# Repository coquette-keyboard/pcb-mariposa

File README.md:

# mariposa-pcb

mariposa is the microcontroller board for the coquette keyboard. note that this project, this board, the associated keyboard shields, and all firmware, is untested and provided with no guarantees or liability for failures, safety hazards, reguatory compliance, and/or injuries and/or losses in any form.

## bill of materials

- Raytac MTBT53-1M nRF5340 module - this is the microcontroller that runs the keyboard
- TI TPS62842DGRR DCDC converter - chosen for its 60nA quiescent current, this powers it
- TI BQ25170DSGR lipoly charger - charges the battery
- Sharp memory-in-pixel LCD that fits on top and has the 10-pin connection that matches the pinout, a few sizes should work
- 2 TI LM66100DCK ideal diode ICs - used to implement ORing between the battery and USB
- 1 TI TPS22917DBV - high side load switch for addressable RGB power. the quiescent on those things is soooooo high relative to the keeb you'll probably want to turn off power completely on battery
- 1 TI SN74LV1T125DCK - converts addressable RGB logic to input voltage for LEDs
- 1 32.768KHz 9pF load cap 3215 2-pin SMD crystal - external LFXO to reduce power use compared to internal oscillator
- 1 TI TSD05C TVS diode, protects USB VBUS input from ESD events
- 4 TI TPD4E1U06 TVS diode arrays, protects exposed data pins + USB data lines from ESD events
- 1 390pF NP0 ceramic capacitor, used to set ARGB power switch slew rate
- 1 560pF NP0 ceramic capacitor, the sharp memory display wants it, idk why
- 3 10nF 0603 ceramic capacitors, two for USB power RC filter, one for battery voltage sampling
- 8 0.1uF 0603 ceramic capacitors, used for decoupling
- 9 1uF 0603 ceramic capacitors, used for decoupling
- 3 4.7uF 1206 ceramic capacitors, used for decoupling
- 2 10uF 0805 ceramic capacitors - decopling, but more power!
- 1 R2.2 0805 thick film resistor, VBUS input surge protection
- 1 0603 1% resistor for DCDC vset, 0R - 1.8V, 1.74k - 2.2V, 21.5k - 3V, 28.7k - 3.1V, 38.3k - 3.2V, 52.3k - 3.3V – use 52.3k if you want accessories that use power to work, but 2.2V is probably the most efficient if no screen, no add-ons, no display, and no UV underglow on גחלילית או פרפר 
- 1 0603 1% resistor for charger VSET, 27k for 4.2V, 36k for 4.1V which will prolong battery longevity at the expense of runtime but this thing should last ages anyway. up to you.
- 1 2xR27 2x0603 convex resistor array - impedance matching USB data pair
- 1 0603 1% resistor for charger ISET, formula is 300/resistor in kohm = charge current in mA. i'm using 1.8k for 167mA charge current. most batteries it is dangerous to exceed 1C (charge current in mA = battery capacity in mAh)
- 2 R620 0805 thick film resistors, one for current limiting LED data output, one for current limiting status LED
- 1 2x whatever 2x0603 convex resistor array - marked as 2.2k as good value, but hard package to find so use whatever, it's just current limiting a couple button inputs as a safety measure
- 2 5.1k 0603 resistors, identify USB-C device
- 1 7.5M 0805 1% or better resistor - one leg of battery level voltage divider
- 1 15M 1206 1% or better resistor - the other leg of battery level voltage divider
- 1 2x10k or 2x4.7k (or really do some math) 2x0402 convex resistor array - optional, i2c pullups, value depends on speed
- 2 10k*4 4x0603 resistor arrays - a few uses, mostly pulling up or down pins
- 1 2xR33 2x0603 convex resistor array - terminating i2c and SWD
- 2 10uH 0603 - nRF internal DCDC
- 1 2.2uH 1008/2520 inductor - DCDC
- 2 1206 ferrites - 60-120 Ohm or so should be good, USB power and shell filtering
- 2 0805 ferrites - 240 Ohm or so is fine and better for noise, much less current here, LCD analog power filtering
- 2 G-Switch GT-TC041B-H036-L1N - side mount tactile switches for power and reset buttons
- 1 of the most common top-mount SMD USB 2.0 USB-C connector there is. take your pick, seriously, they almost all will fit but the GCT USB4105 is the one the footprint's actually meant for 
- 1 2-pin horizontal PicoBlade connector - battery input
- 1 28-pin 0.5mm pitch FFC SMD connector - output to keyboard, be sure the mounting legs will fit
- 1 10-pin 0.5mm pitch FPC SMD connector - output to LCD, be sure the mounting legs will fit
- 1 JST_SH_SM03B-SRSS-TB_1x03 or similar - ARGB output
- 1 JST_SH_SM04B-SRSS-TB_1x04 or similar - Adafruit Stemma QT-like i2c output
- 1 JST_SH_SM08B-SRSS-TB_1x08 or similar - Pimoroni SP/CE-like SPI and PWM output
- 1 shitty add-on SMD connector - for Hackaday v1.69bis shitty add ons
- 6 SK6805-EC14 ARGB LEDs - picked for the 0.25mA quiescent, still even at 0% brightness the 1.5mA total will drain a 250mAh battery in under a day. be sure you use the load switch wisely
- 1 0805 LED - for a status light. have fun!

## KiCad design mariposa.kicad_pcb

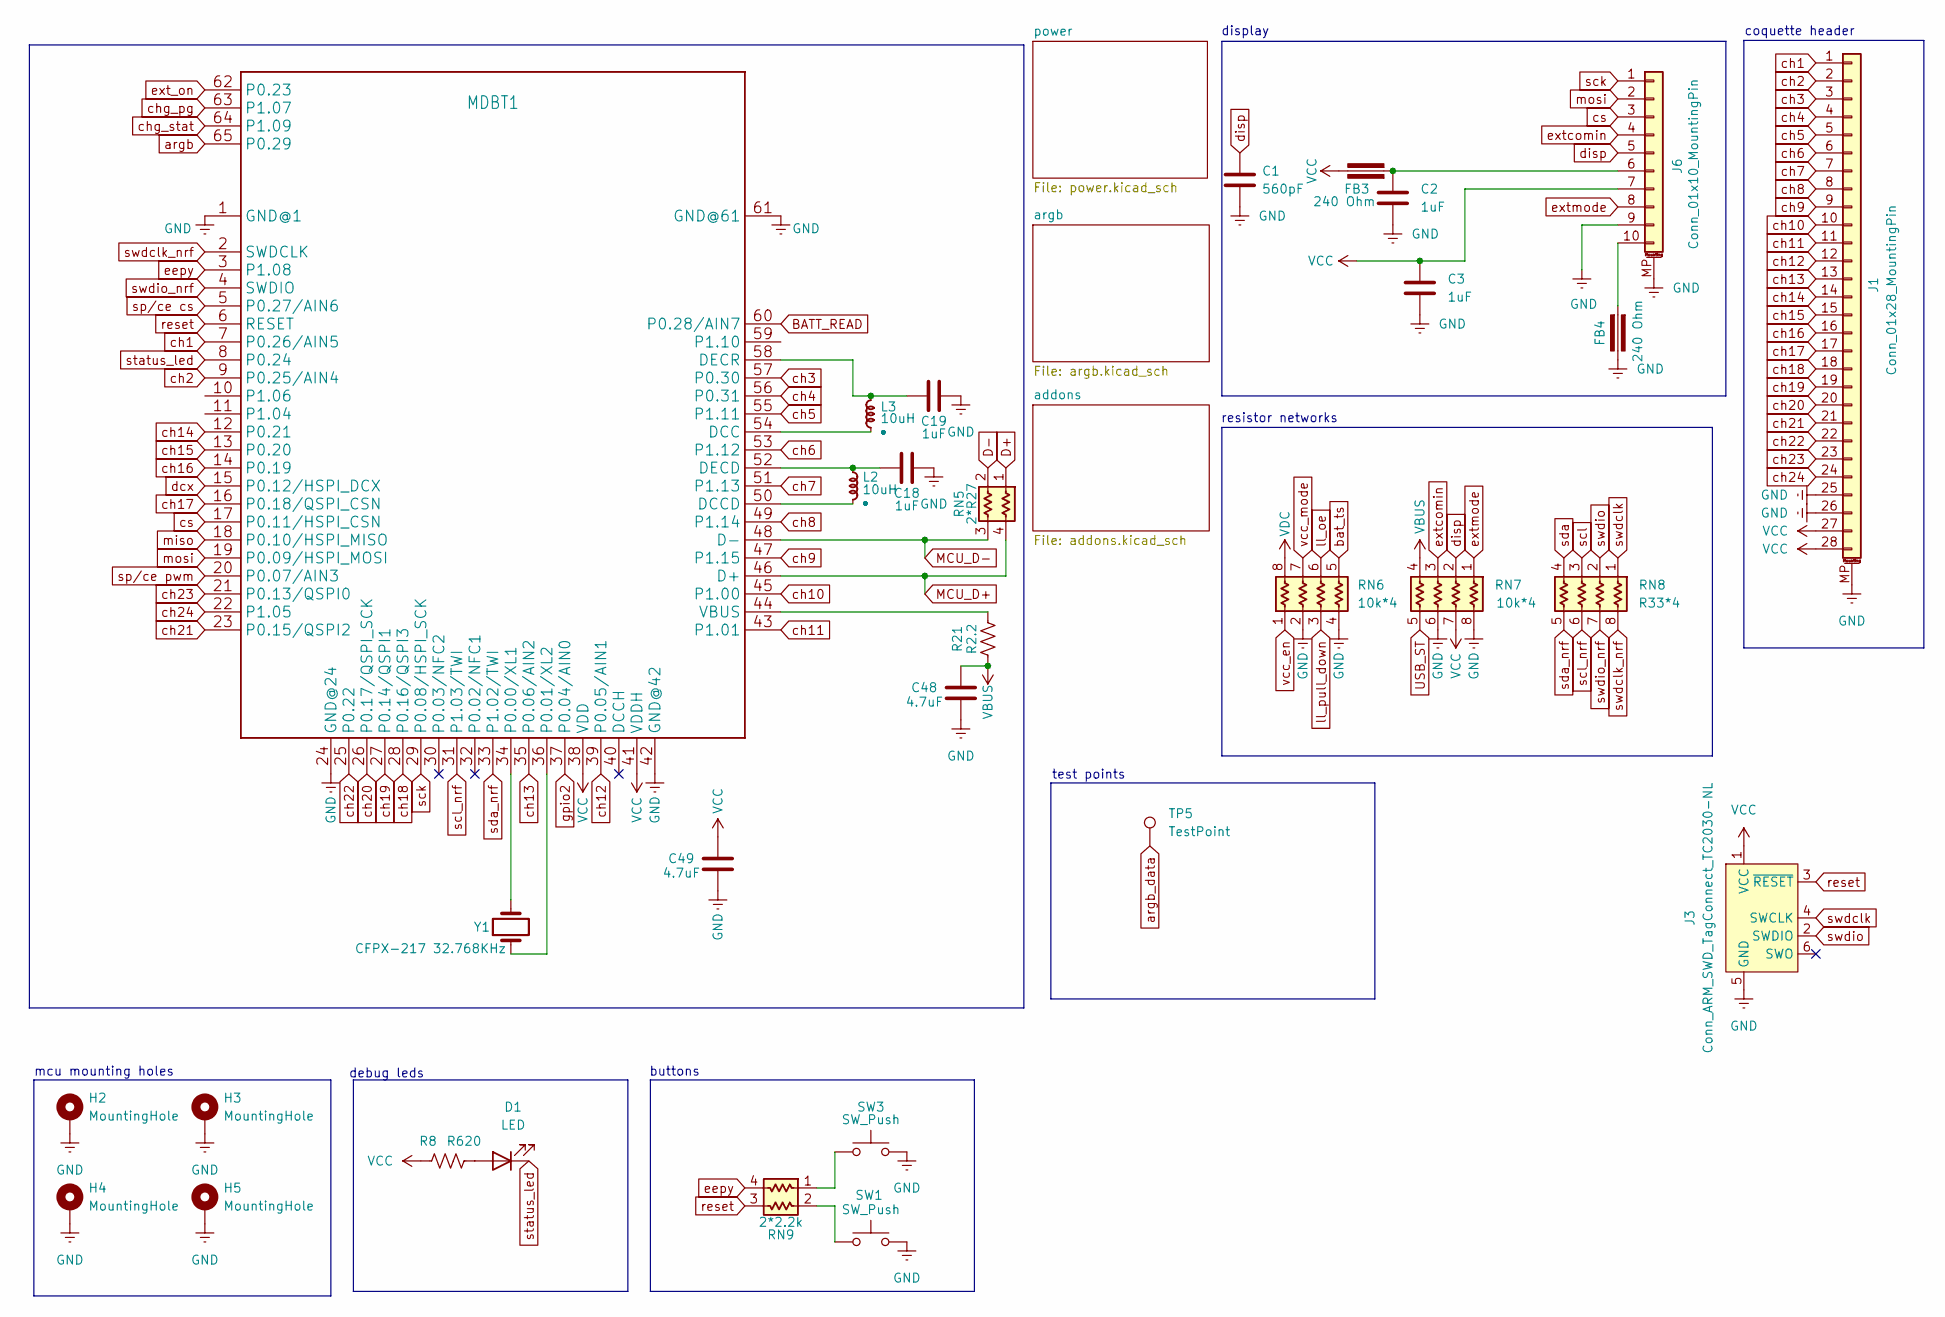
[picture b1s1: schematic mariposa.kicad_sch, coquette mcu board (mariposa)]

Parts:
C1: 560pF; C_0603_1608Metric
C2, C3, C18, C19: 1uF; C_0603_1608Metric
C48, C49: 4.7uF; C_1206_3216Metric
D1: LED; LED_0603_1608Metric
FB3, FB4: 240 Ohm; Ferrite_0603_1608Metric
H2, H3, H4, H5: MountingHole; MountingHole_3.2mm_M3_DIN965_Pad
J1: Conn_01x28_MountingPin; Hirose_FH12-28S-0.5SH_1x28-1MP_P0.50mm_Horizontal
J3: Conn_ARM_SWD_TagConnect_TC2030-NL; Tag-Connect_TC2030-IDC-NL_2x03_P1.27mm_Vertical
J6: Conn_01x10_MountingPin; Hirose_FH12-10S-0.5SH_1x10-1MP_P0.50mm_Horizontal
L2, L3: 10uH; L_0603_1608Metric
MDBT1: MDBT53
R8: R620; R_0603_1608Metric
R21: R2.2; R_0805_2012Metric
RN5: 2*R27; R_Array_Convex_2x0603
RN6, RN7: 10k*4; R_Array_Convex_4x0603
RN8: R33*4; R_Array_Convex_4x0603
RN9: 2*2.2k; R_Array_Convex_2x0603
SW1, SW3: SW_Push; G-Switch GT-TC041B-H036-L1N
TP5: TestPoint; TestPoint_Pad_D1.0mm
Y1: CFPX-217 32.768KHz; Crystal_SMD_3215-2Pin_3.2x1.5mm

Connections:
BATT_READ: MDBT1.60 (P0.28/AIN7); also elsewhere on the board
D+: RN5.1 (R1.1); also elsewhere on the board
D-: RN5.2 (R2.1); also elsewhere on the board
GND: C1.2, C2.2, C3.2, C18.1, C19.1, C48.1, C49.1, FB4.2, H2.1, H3.1, H4.1, H5.1, J1.25, J1.26, J1.MP (MountPin), J3.5 (GND), J6.9, J6.MP (MountPin), MDBT1.1 (GND@1), MDBT1.24 (GND@24), MDBT1.42 (GND@42), MDBT1.61 (GND@61), RN6.2 (R2.1), RN6.4 (R4.1), RN7.6 (R3.2), RN7.8 (R1.2), SW1.2, SW3.2; also elsewhere on the board
MCU_D+: MDBT1.46 (D+), RN5.4 (R1.2)
MCU_D-: MDBT1.48 (D-), RN5.3 (R2.2)
unnamed: D1.2 (A), R8.1
unnamed: C2.1, FB3.1, J6.6
unnamed: FB4.1, J6.10
unnamed: C18.2, L2.1 (+), MDBT1.52 (DECD)
unnamed: L2.2 (-), MDBT1.50 (DCCD)
unnamed: L3.1 (+), MDBT1.54 (DCC)
unnamed: C19.2, L3.2 (-), MDBT1.58 (DECR)
unnamed: MDBT1.34 (P0.00/XL1), Y1.2
unnamed: MDBT1.36 (P0.01/XL2), Y1.1
unnamed: MDBT1.44 (VBUS), R21.1
unnamed: RN9.1 (R1.1), SW3.1
unnamed: RN9.2 (R2.1), SW1.1
USB_ST: RN7.5 (R4.2); also elsewhere on the board
VBUS: C48.2, R21.2, RN7.4 (R4.1); also elsewhere on the board
VCC: C3.1, C49.2, FB3.2, J1.27, J1.28, J3.1 (VCC), J6.7, MDBT1.38 (VDD), MDBT1.41 (VDDH), R8.2, RN7.7 (R2.2); also elsewhere on the board
VDC: RN6.8 (R1.2); also elsewhere on the board
argb: MDBT1.65 (P0.29); also elsewhere on the board
argb_data: TP5.1; also elsewhere on the board
bat_ts: RN6.5 (R4.2); also elsewhere on the board
ch1: J1.1, MDBT1.7 (P0.26/AIN5)
ch2: J1.2, MDBT1.9 (P0.25/AIN4)
ch3: J1.3, MDBT1.57 (P0.30)
ch4: J1.4, MDBT1.56 (P0.31)
ch5: J1.5, MDBT1.55 (P1.11)
ch6: J1.6, MDBT1.53 (P1.12)
ch7: J1.7, MDBT1.51 (P1.13)
ch8: J1.8, MDBT1.49 (P1.14)
ch9: J1.9, MDBT1.47 (P1.15)
ch10: J1.10, MDBT1.45 (P1.00)
ch11: J1.11, MDBT1.43 (P1.01)
ch12: J1.12, MDBT1.39 (P0.05/AIN1)
ch13: J1.13, MDBT1.35 (P0.06/AIN2)
ch14: J1.14, MDBT1.12 (P0.21)
ch15: J1.15, MDBT1.13 (P0.20)
ch16: J1.16, MDBT1.14 (P0.19)
ch17: J1.17, MDBT1.16 (P0.18/QSPI_CSN)
ch18: J1.18, MDBT1.28 (P0.16/QSPI3)
ch19: J1.19, MDBT1.27 (P0.14/QSPI1)
ch20: J1.20, MDBT1.26 (P0.17/QSPI_SCK)
ch21: J1.21, MDBT1.23 (P0.15/QSPI2)
ch22: J1.22, MDBT1.25 (P0.22)
ch23: J1.23, MDBT1.21 (P0.13/QSPI0)
ch24: J1.24, MDBT1.22 (P1.05)
chg_pg: MDBT1.63 (P1.07); also elsewhere on the board
chg_stat: MDBT1.64 (P1.09); also elsewhere on the board
cs: J6.3, MDBT1.17 (P0.11/HSPI_CSN)
dcx: MDBT1.15 (P0.12/HSPI_DCX)
disp: C1.1, J6.5, RN7.2 (R2.1)
eepy: MDBT1.3 (P1.08), RN9.4 (R1.2)
ext_on: MDBT1.62 (P0.23); also elsewhere on the board
extcomin: J6.4, RN7.3 (R3.1)
extmode: J6.8, RN7.1 (R1.1)
gpio2: MDBT1.37 (P0.04/AIN0); also elsewhere on the board
ll_oe: RN6.6 (R3.2); also elsewhere on the board
ll_pull_down: RN6.3 (R3.1); also elsewhere on the board
miso: MDBT1.18 (P0.10/HSPI_MISO); also elsewhere on the board
mosi: J6.2, MDBT1.19 (P0.09/HSPI_MOSI); also elsewhere on the board
reset: J3.3 (~RESET), MDBT1.6 (RESET), RN9.3 (R2.2); also elsewhere on the board
sck: J6.1, MDBT1.29 (P0.08/HSPI_SCK); also elsewhere on the board
scl: RN8.3 (R3.1); also elsewhere on the board
scl_nrf: MDBT1.31 (P1.03/TWI), RN8.6 (R3.2)
sda: RN8.4 (R4.1); also elsewhere on the board
sda_nrf: MDBT1.33 (P1.02/TWI), RN8.5 (R4.2)
sp/ce cs: MDBT1.5 (P0.27/AIN6); also elsewhere on the board
sp/ce pwm: MDBT1.20 (P0.07/AIN3); also elsewhere on the board
status_led: D1.1 (K), MDBT1.8 (P0.24)
swdclk: J3.4 (SWCLK), RN8.1 (R1.1); also elsewhere on the board
swdclk_nrf: MDBT1.2 (SWDCLK), RN8.8 (R1.2)
swdio: J3.2 (SWDIO), RN8.2 (R2.1); also elsewhere on the board
swdio_nrf: MDBT1.4 (SWDIO), RN8.7 (R2.2)
vcc_en: RN6.1 (R1.1); also elsewhere on the board
vcc_mode: RN6.7 (R2.2); also elsewhere on the board

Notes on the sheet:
buttons
test points
display
coquette header
mcu mounting holes
debug leds
resistor networks

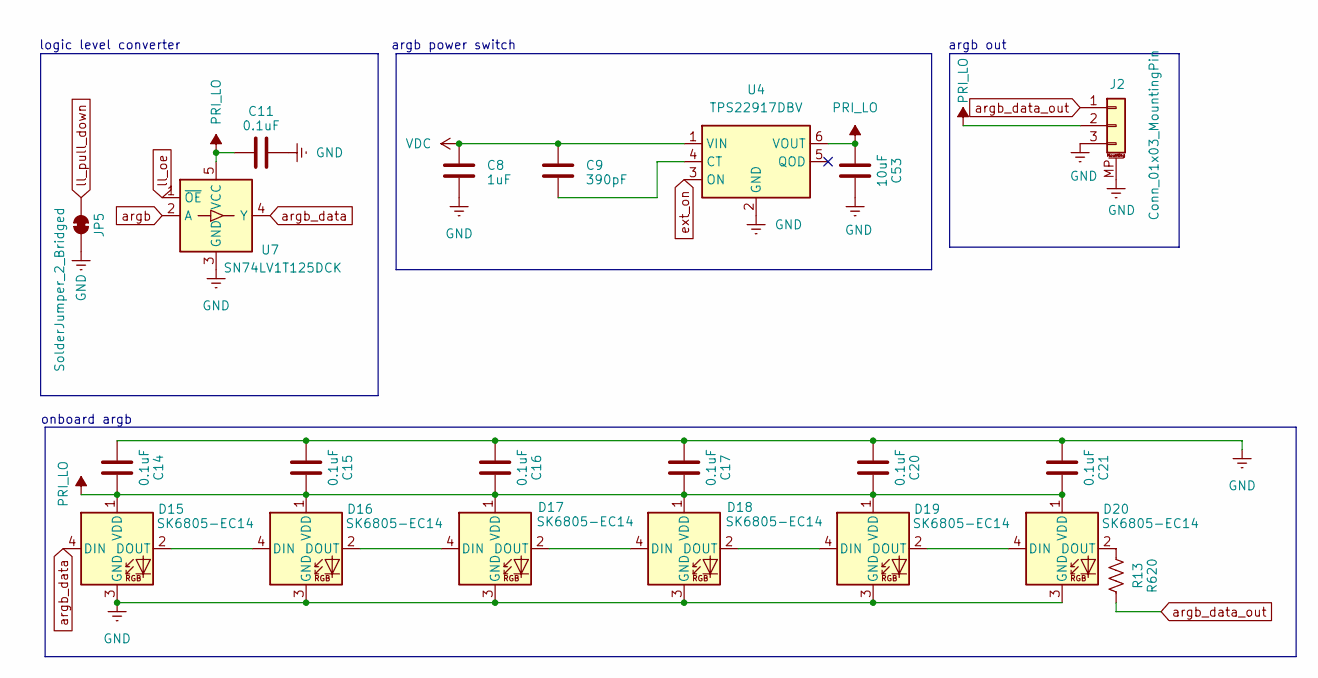
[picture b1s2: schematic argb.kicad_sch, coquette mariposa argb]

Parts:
C8: 1uF; C_0603_1608Metric
C9: 390pF; C_0603_1608Metric
C11, C14, C15, C16, C17, C20, C21: 0.1uF; C_0603_1608Metric
C53: 10uF; C_0603_1608Metric
D15, D16, D17, D18, D19, D20: SK6805-EC14
J2: Conn_01x03_MountingPin; JST_SH_SM03B-SRSS-TB_1x03-1MP_P1.00mm_Horizontal
JP5: SolderJumper_2_Bridged; SolderJumper-2_P1.3mm_Bridged_RoundedPad1.0x1.5mm
R13: R620; R_0603_1608Metric
U4: TPS22917DBV
U7: SN74LV1T125DCK

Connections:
GND: C8.2, C11.2, C14.1, C15.1, C16.1, C17.1, C20.1, C21.1, C53.2, D15.3 (GND), D16.3 (GND), D17.3 (GND), D18.3 (GND), D19.3 (GND), D20.3 (GND), J2.3, J2.MP (MountPin), JP5.2 (B), U4.2 (GND), U7.3 (GND); also elsewhere on the board
unnamed: D15.2 (DOUT), D16.4 (DIN)
unnamed: D16.2 (DOUT), D17.4 (DIN)
unnamed: D17.2 (DOUT), D18.4 (DIN)
unnamed: D18.2 (DOUT), D19.4 (DIN)
unnamed: D19.2 (DOUT), D20.4 (DIN)
unnamed: D20.2 (DOUT), R13.2
unnamed: C9.2, U4.4 (CT)
PRI_LO: C11.1, C14.2, C15.2, C16.2, C17.2, C20.2, C21.2, C53.1, D15.1 (VDD), D16.1 (VDD), D17.1 (VDD), D18.1 (VDD), D19.1 (VDD), D20.1 (VDD), J2.2, U4.6 (VOUT), U7.5 (VCC)
VDC: C8.1, C9.1, U4.1 (VIN); also elsewhere on the board
argb: U7.2 (A); also elsewhere on the board
argb_data: D15.4 (DIN), U7.4 (Y); also elsewhere on the board
argb_data_out: J2.1, R13.1; also elsewhere on the board
ext_on: U4.3 (ON); also elsewhere on the board
ll_oe: U7.1 (~OE); also elsewhere on the board
ll_pull_down: JP5.1 (A); also elsewhere on the board

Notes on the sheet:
onboard argb
argb power switch
logic level converter
argb out

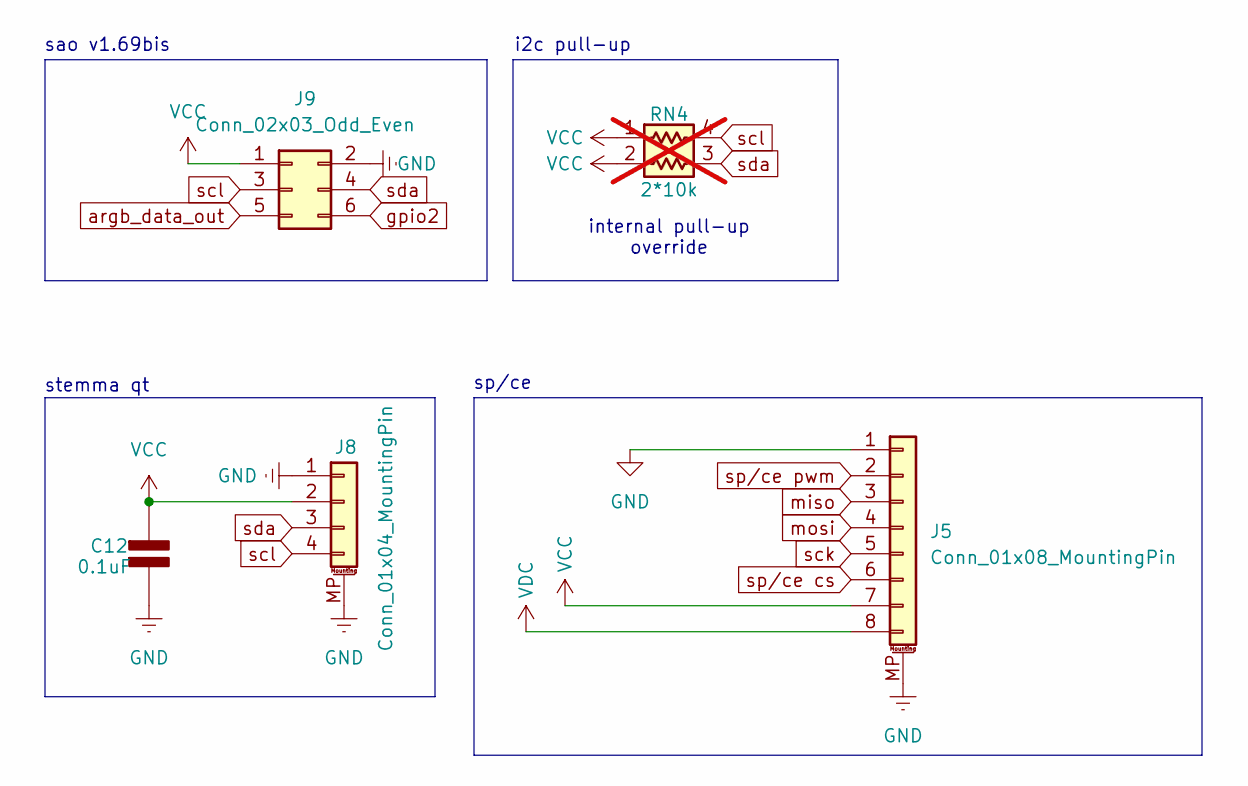
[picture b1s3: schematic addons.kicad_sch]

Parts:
C12: 0.1uF; C_0603_1608Metric; Rating V
J5: Conn_01x08_MountingPin; JST_SH_SM08B-SRSS-TB_1x08-1MP_P1.00mm_Horizontal
J8: Conn_01x04_MountingPin; JST_SH_SM04B-SRSS-TB_1x04-1MP_P1.00mm_Horizontal
J9: Conn_02x03_Odd_Even; PinSocket_2x03_P2.54mm_Vertical_SMD
RN4: 2*10k; R_Array_Convex_2x0402; not fitted

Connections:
GND: C12.2 (-), J5.1, J5.MP (MountPin), J8.1, J8.MP (MountPin), J9.2; also elsewhere on the board
VCC: C12.1 (+), J5.7, J8.2, J9.1, RN4.1 (R1.1), RN4.2 (R2.1); also elsewhere on the board
VDC: J5.8; also elsewhere on the board
argb_data_out: J9.5; also elsewhere on the board
gpio2: J9.6; also elsewhere on the board
miso: J5.3; also elsewhere on the board
mosi: J5.4; also elsewhere on the board
sck: J5.5; also elsewhere on the board
scl: J8.4, J9.3, RN4.4 (R1.2); also elsewhere on the board
sda: J8.3, J9.4, RN4.3 (R2.2); also elsewhere on the board
sp/ce cs: J5.6; also elsewhere on the board
sp/ce pwm: J5.2; also elsewhere on the board

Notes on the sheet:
sao v1.69bis
stemma qt
sp/ce
internal pull-up override
i2c pull-up

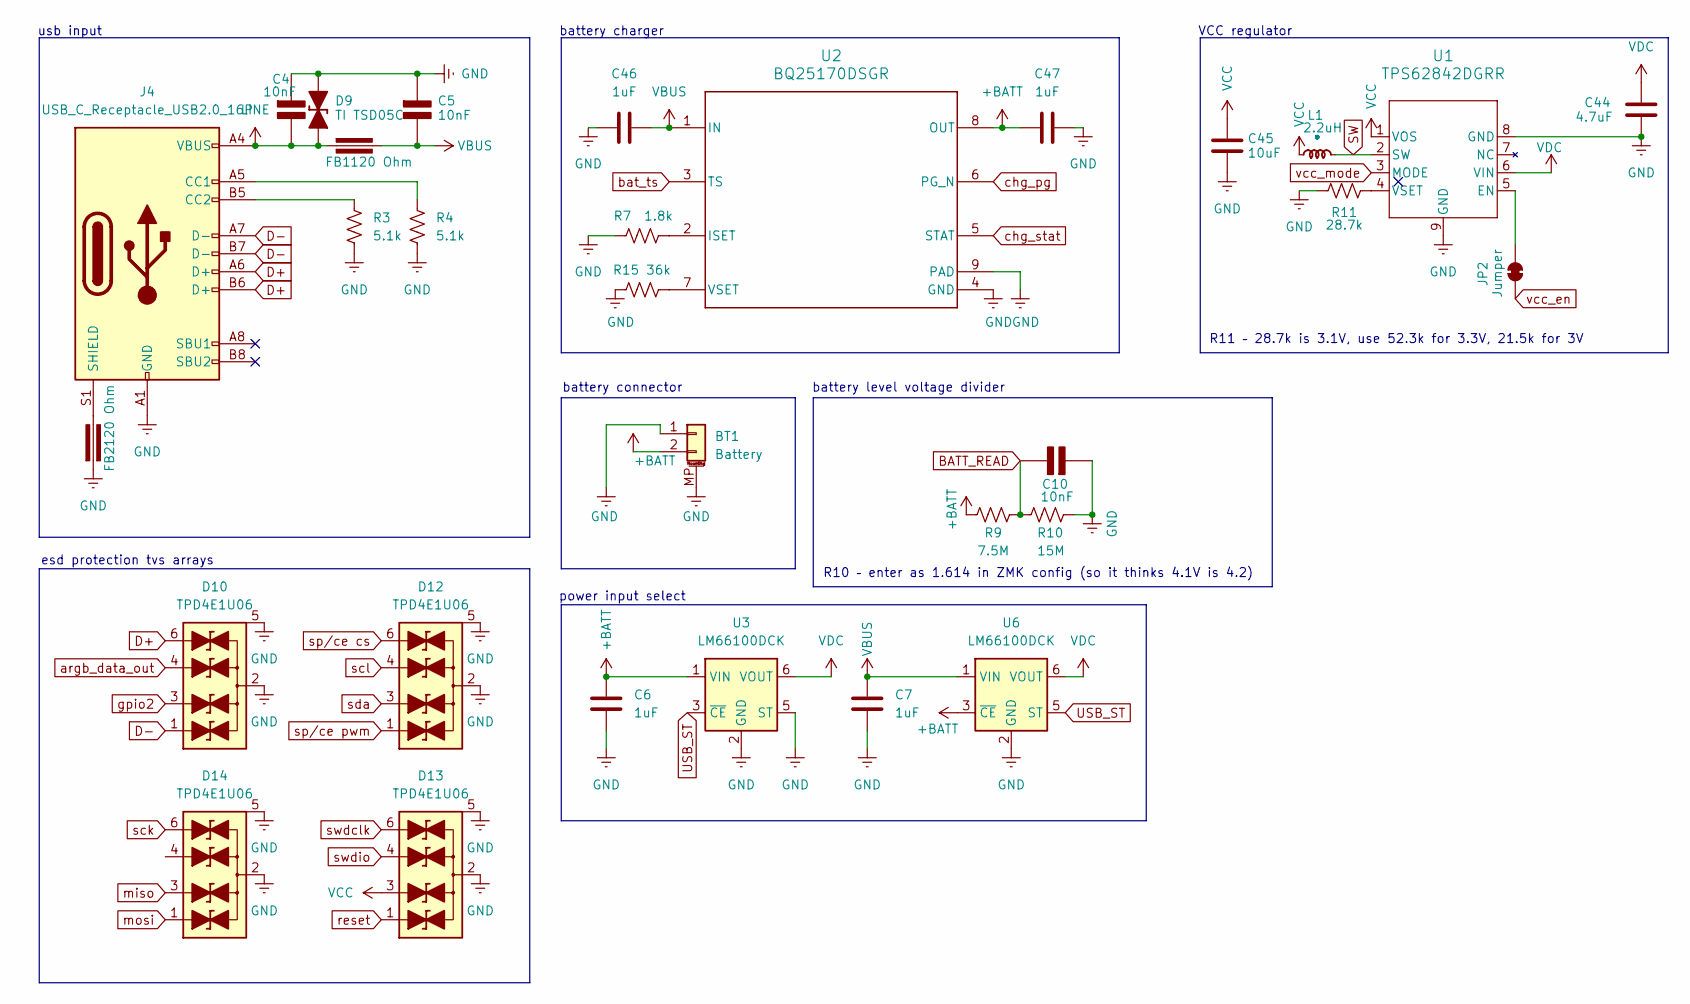
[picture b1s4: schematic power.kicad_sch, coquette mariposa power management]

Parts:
BT1: Battery; Molex_PicoBlade_53261-0271_1x02-1MP_P1.25mm_Horizontal
C4, C5, C10: 10nF; C_0603_1608Metric; Rating V
C6, C7, C46, C47: 1uF; C_0603_1608Metric
C44: 4.7uF; C_1206_3216Metric
C45: 10uF; C_0805_2012Metric
D9: TI TSD05C; TSD05C
D10, D12, D13, D14: TPD4E1U06
FB1, FB2: 120 Ohm; Ferrite_1206_3216Metric
J4: USB_C_Receptacle_USB2.0_16P; USB_C_Receptacle_GCT_USB4105-xx-A_16P_TopMnt_Horizontal
JP2: Jumper; SolderJumper-2_P1.3mm_Bridged_RoundedPad1.0x1.5mm
L1: 2.2uH; L_1008_2520Metric
R3, R4: 5.1k; R_0603_1608Metric
R7: 1.8k; R_0603_1608Metric
R9: 7.5M; R_0603_1608Metric
R10: 15M; R_1206_3216Metric
R11: 28.7k; R_0603_1608Metric
R15: 36k; R_0603_1608Metric
U1: TPS62842DGRR; HVSSOP-8-1EP_3x3mm_P0.65mm_EP1.57x1.89mm_ThermalVias
U2: BQ25170DSGR; DSG0008A
U3, U6: LM66100DCK

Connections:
+BATT: BT1.2, C6.1, C47.1, R9.2, U2.8 (OUT), U3.1 (VIN), U6.3 (~CE)
BATT_READ: C10.1 (+), R9.1, R10.2; also elsewhere on the board
D+: D10.6 (L4), J4.A6 (D+), J4.B6 (D+); also elsewhere on the board
D-: D10.1 (L1), J4.A7 (D-), J4.B7 (D-); also elsewhere on the board
GND: BT1.1, BT1.MP (MountPin), C4.1 (+), C5.1 (+), C6.2, C7.2, C10.2 (-), C44.2, C45.2, C46.1, C47.2, D9.1 (K), D10.2 (VN), D10.5 (NC), D12.2 (VN), D12.5 (NC), D13.2 (VN), D13.5 (NC), D14.2 (VN), D14.5 (NC), FB2.1, J4.A1 (GND), J4.A12 (GND), J4.B1 (GND), J4.B12 (GND), R3.2, R4.2, R7.2, R10.1, R11.2, R15.2, U1.8 (GND), U1.9 (GND), U2.4 (GND), U2.9 (PAD), U3.2 (GND), U3.5 (ST), U6.2 (GND); also elsewhere on the board
LINE: C4.2 (-), D9.2 (A), FB1.1, J4.A4 (VBUS), J4.A9 (VBUS), J4.B4 (VBUS), J4.B9 (VBUS)
unnamed: J4.A5 (CC1), R4.1
unnamed: J4.B5 (CC2), R3.1
unnamed: FB2.2, J4.S1 (SHIELD)
unnamed: JP2.1 (A), U1.5 (EN)
unnamed: R11.1, U1.4 (VSET)
unnamed: R7.1, U2.2 (ISET)
unnamed: R15.1, U2.7 (VSET)
SW: L1.2 (-), U1.2 (SW)
USB_ST: U3.3 (~CE), U6.5 (ST); also elsewhere on the board
VBUS: C5.2 (-), C7.1, C46.2, FB1.2, U2.1 (IN), U6.1 (VIN); also elsewhere on the board
VCC: C45.1, D13.3 (L2), L1.1 (+), U1.1 (VOS); also elsewhere on the board
VDC: C44.1, U1.6 (VIN), U3.6 (VOUT), U6.6 (VOUT); also elsewhere on the board
argb_data_out: D10.4 (L3); also elsewhere on the board
bat_ts: U2.3 (TS); also elsewhere on the board
chg_pg: U2.6 (PG_N); also elsewhere on the board
chg_stat: U2.5 (STAT); also elsewhere on the board
gpio2: D10.3 (L2); also elsewhere on the board
miso: D14.3 (L2); also elsewhere on the board
mosi: D14.1 (L1); also elsewhere on the board
reset: D13.1 (L1); also elsewhere on the board
sck: D14.6 (L4); also elsewhere on the board
scl: D12.4 (L3); also elsewhere on the board
sda: D12.3 (L2); also elsewhere on the board
sp/ce cs: D12.6 (L4); also elsewhere on the board
sp/ce pwm: D12.1 (L1); also elsewhere on the board
swdclk: D13.6 (L4); also elsewhere on the board
swdio: D13.4 (L3); also elsewhere on the board
vcc_en: JP2.2 (B); also elsewhere on the board
vcc_mode: U1.3 (MODE); also elsewhere on the board

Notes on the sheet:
R11 – 28.7k is 3.1V, use 52.3k for 3.3V, 21.5k for 3V
esd protection tvs arrays
R10 – enter as 1.614 in ZMK config (so it thinks 4.1V is 4.2)
battery connector
battery charger
power input select
usb input
battery level voltage divider
VCC regulator

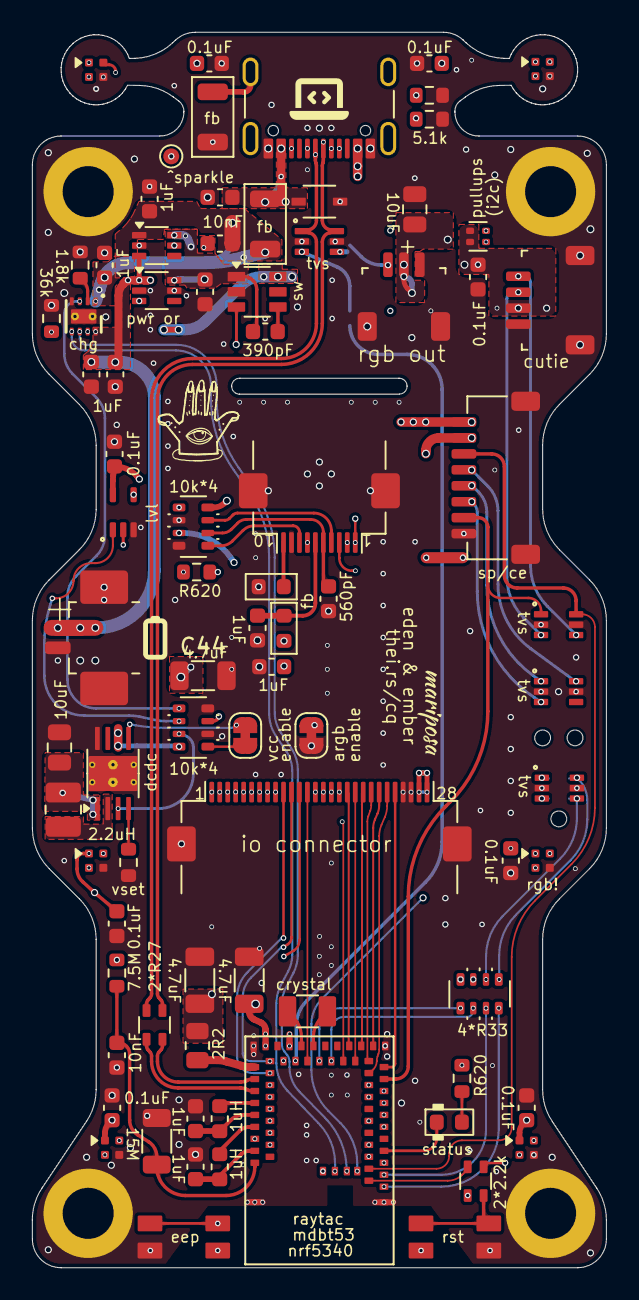
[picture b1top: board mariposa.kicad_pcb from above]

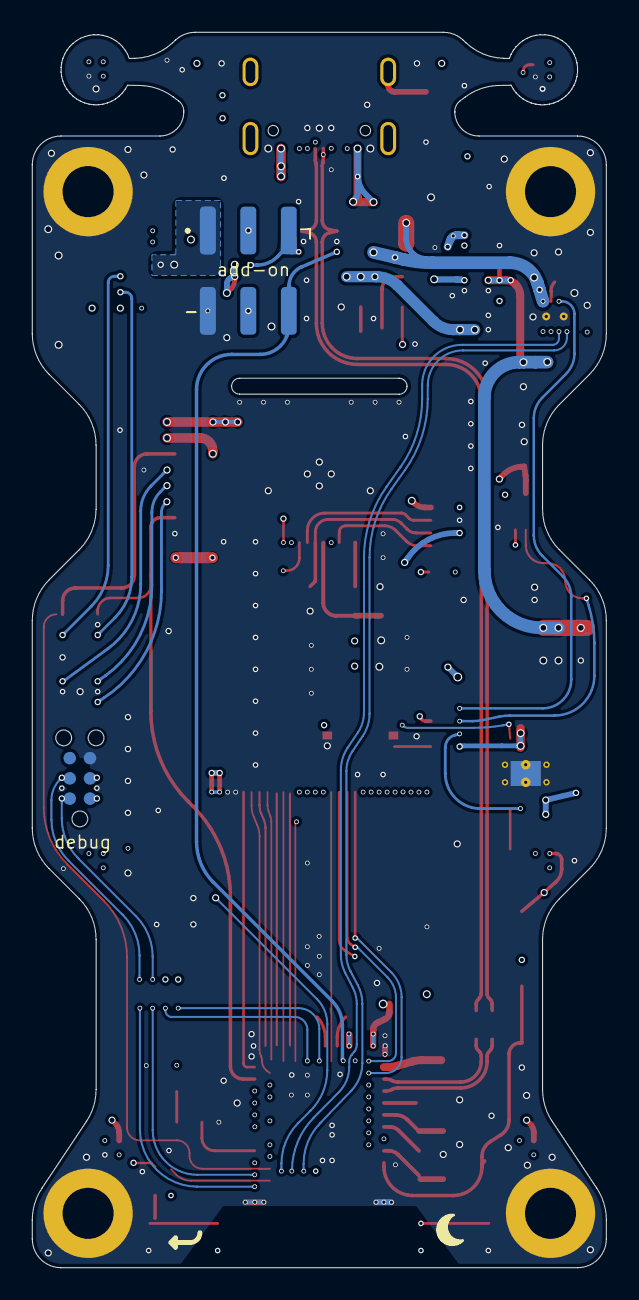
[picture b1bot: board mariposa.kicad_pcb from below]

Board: 6 copper layers, 36.0 x 77.5 mm, 88 parts (6 on the bottom side), 96 nets.

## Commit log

2025-01-08 mariposa v2 RC1
2025-01-16 mariposa v2 RC2
2025-01-19 mariposa v2 RC3
2025-01-19 parpar mariposa mk2 rc6
2025-01-19 remove old files
2025-01-19 parpar mariposa mk2 rc7
2025-01-19 parpar mariposa mk2 rc8
2025-01-19 coquette mariposa mk2 final?
2025-01-19 update bom
2025-01-20 really final?
2025-01-20 another resistor value to a real-world existing part
2025-01-21 actually production version, for real?
2025-01-21 the final, actual, mk2 production files
2025-01-23 the final, actual, mk2 production files for real
2025-02-01 mariposa v2 pre
2025-02-02 update date
2025-02-02 title page 3 of schematic
2025-02-03 final to order
2025-03-08 cleanup
2025-03-26 v3 efforts
2025-04-01 more rounding
2025-04-04 nearing the end
2025-04-18 progress
2025-04-19 new dcdc
2025-04-19 new dcdc rerouting
2025-05-02 tweaks
2025-05-11 maybe order?
2025-05-11 jlc order
2025-05-19 ordered
2025-05-27 minor tweaks for nrf5340 rev
2025-06-04 fix crystal routing clearance
2025-06-07 improve routing and silkscreen
2025-06-07 update gitignore
2025-06-11 minor tweaks
2025-06-15 updated readme, tweaked routing
2025-06-15 fixes
2025-06-19 clearances
2025-06-19 add prl
2025-06-20 trying stm32 layout
